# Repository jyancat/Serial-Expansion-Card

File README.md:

Design files for my DB9 RS232 Expansion Card 

JLCPCB production files are generated by [Bouni's JLCPCB tools plugin](https://github.com/bouni/kicad-jlcpcb-tools)

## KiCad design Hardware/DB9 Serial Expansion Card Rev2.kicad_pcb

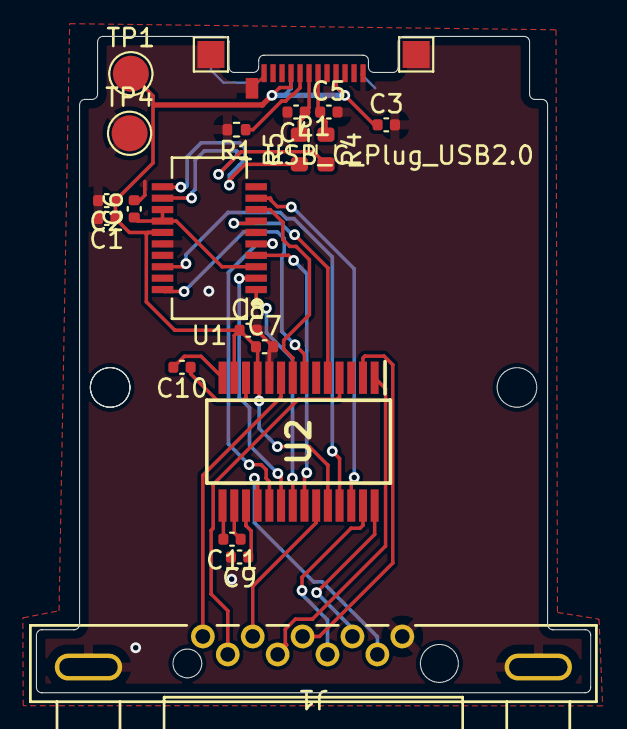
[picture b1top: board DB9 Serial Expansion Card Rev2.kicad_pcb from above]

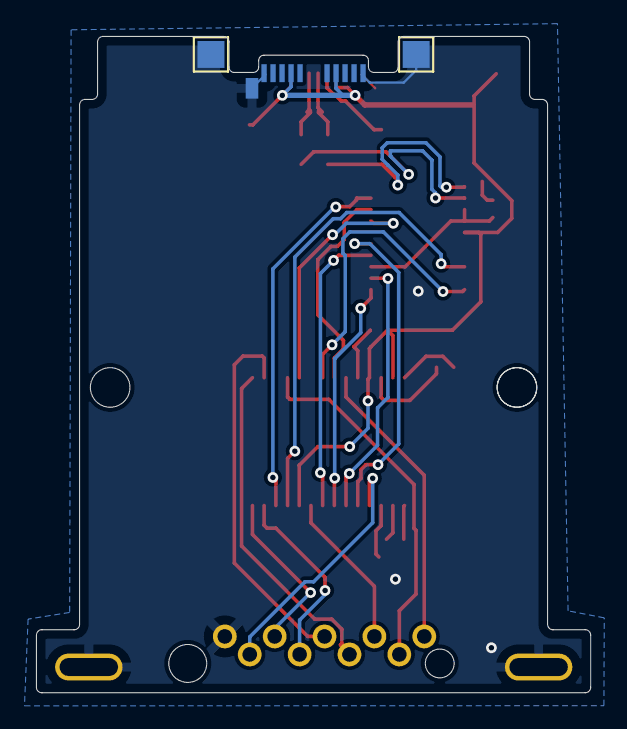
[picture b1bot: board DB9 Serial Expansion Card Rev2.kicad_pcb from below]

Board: 2 copper layers, 30.8 x 36.5 mm, 27 parts (2 on the bottom side), 28 nets.

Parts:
C1, C6, C7, C8, C10: 100nF; C_0402_1005Metric
C2: 4.7uF; C_0402_1005Metric
C3: 10nF; C_0402_1005Metric
C4, C5: 47pF; C_0402_1005Metric
C9, C11: 100nF, 16v; C_0402_1005Metric
H1, H1#2, H2: MountingHole; MountingHole_2.2mm_M2
J1: DE9_Receptacle; CONN9_K31X_KYC
P1: USB_C_Plug_USB2.0; USB_C_Plug_Molex_105444
R1: 5.1k; R_0402_1005Metric
R4, R5: 27R; R_0603_1608Metric
TP1, TP2, TP3, TP4#2: TestPoint; TestPoint_Pad_1.5x1.5mm
TP1#2, TP4: TestPoint; TestPoint_Pad_D2.0mm
U1: FT231XS; SSOP-20_3.9x8.7mm_P0.635mm
U2: SP213ECA-L_TR; SOP65P780X200-28N

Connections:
3V3OUT: C6.1, U1.3 (VCCIO), U1.13 (3V3OUT), U1.14 (~RESET)
/D+: C4.1, P1.A6 (D+), R5.1, R5.2, U1.11 (USBDP)
/D-: C5.1, P1.A7 (D-), R4.1, R4.2, U1.12 (USBDM)
CTS: J1.8, U2.27 (R3IN)
DCD: J1.1, U2.9 (R1IN)
DSR: J1.6, U2.4 (R2IN)
DTR: J1.4, U2.28 (T4OUT)
Earth: C1.2, C2.2, C3.2, C4.2, C5.2, C6.2, C7.2, C8.2, C9.2, J1.5, J1.10 (5), J1.11 (5), P1.A1 (GND), P1.A12 (GND), P1.B1 (GND), P1.B12 (GND), P1.S1 (SHIELD), R1.2, TP1.1, TP2.1, TP3.1, TP4.1, TP4#2.1, U1.6 (GND), U1.16 (GND), U2.10 (GND)
unnamed: P1.A5 (CC), R1.1
unnamed: C10.1, U2.12 (C1+)
unnamed: C10.2, U2.14 (C1-)
unnamed: C11.2, U2.15 (C2+)
unnamed: C11.1, U2.16 (C2-)
unnamed: C9.1, U2.17 (V-)
RI: J1.9, U2.18 (R5IN)
RTS: J1.7, U2.1 (T3OUT)
RXD: J1.2, U2.23 (R4IN)
SLEEP#: U1.18 (CBUS0), U2.25 (~SHUTDOWN_(SD))
TXD: J1.3, U2.2 (T1OUT)
USB_RXD: U1.4 (RXD), U2.22 (R4OUT)
USB_TXD: U1.20 (TXD), U2.7 (T1IN)
USB_~CTS: U1.9 (~CTS), U2.26 (R3OUT)
USB_~DCD: U1.8 (~DCD), U2.8 (R1OUT)
USB_~DSR: U1.7 (~DSR), U2.5 (R2OUT)
USB_~DTR: U1.1 (~DTR), U2.21 (T4IN)
USB_~RI: U1.5 (~RI), U2.19 (R5OUT)
USB_~RTS: U1.2 (~RTS), U2.20 (T3IN)
VCC: C1.1, C2.1, C3.1, C7.1, C8.1, P1.A4 (VBUS), P1.A9 (VBUS), P1.B4 (VBUS), P1.B9 (VBUS), TP1#2.1, U1.15 (VCC), U2.11 (VCC), U2.13 (V+), U2.24 (EN)

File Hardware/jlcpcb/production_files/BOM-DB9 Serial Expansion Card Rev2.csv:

Comment,Designator,Footprint,LCSC
FT231XS,U1,SSOP-20_3.9x8.7mm_P0.635mm,C132160
USB_C_Plug_USB2.0,P1,USB_C_Plug_Molex_105444,C134082
10nF,C3,C_0402_1005Metric,C15195
100nF,"C1,C10,C11,C6,C7,C8,C9",C_0402_1005Metric,C1525
SP213ECA-L_TR,U2,SOP65P780X200-28N,C1544521
47pF,"C4,C5",C_0402_1005Metric,C1567
DE9_Receptacle,J1,CONN9_K31X_KYC,C17429472
4.7uF,C2,C_0402_1005Metric,C23733
27R,"R4,R5",R_0603_1608Metric,C25190
5.1k,R1,R_0402_1005Metric,C25905

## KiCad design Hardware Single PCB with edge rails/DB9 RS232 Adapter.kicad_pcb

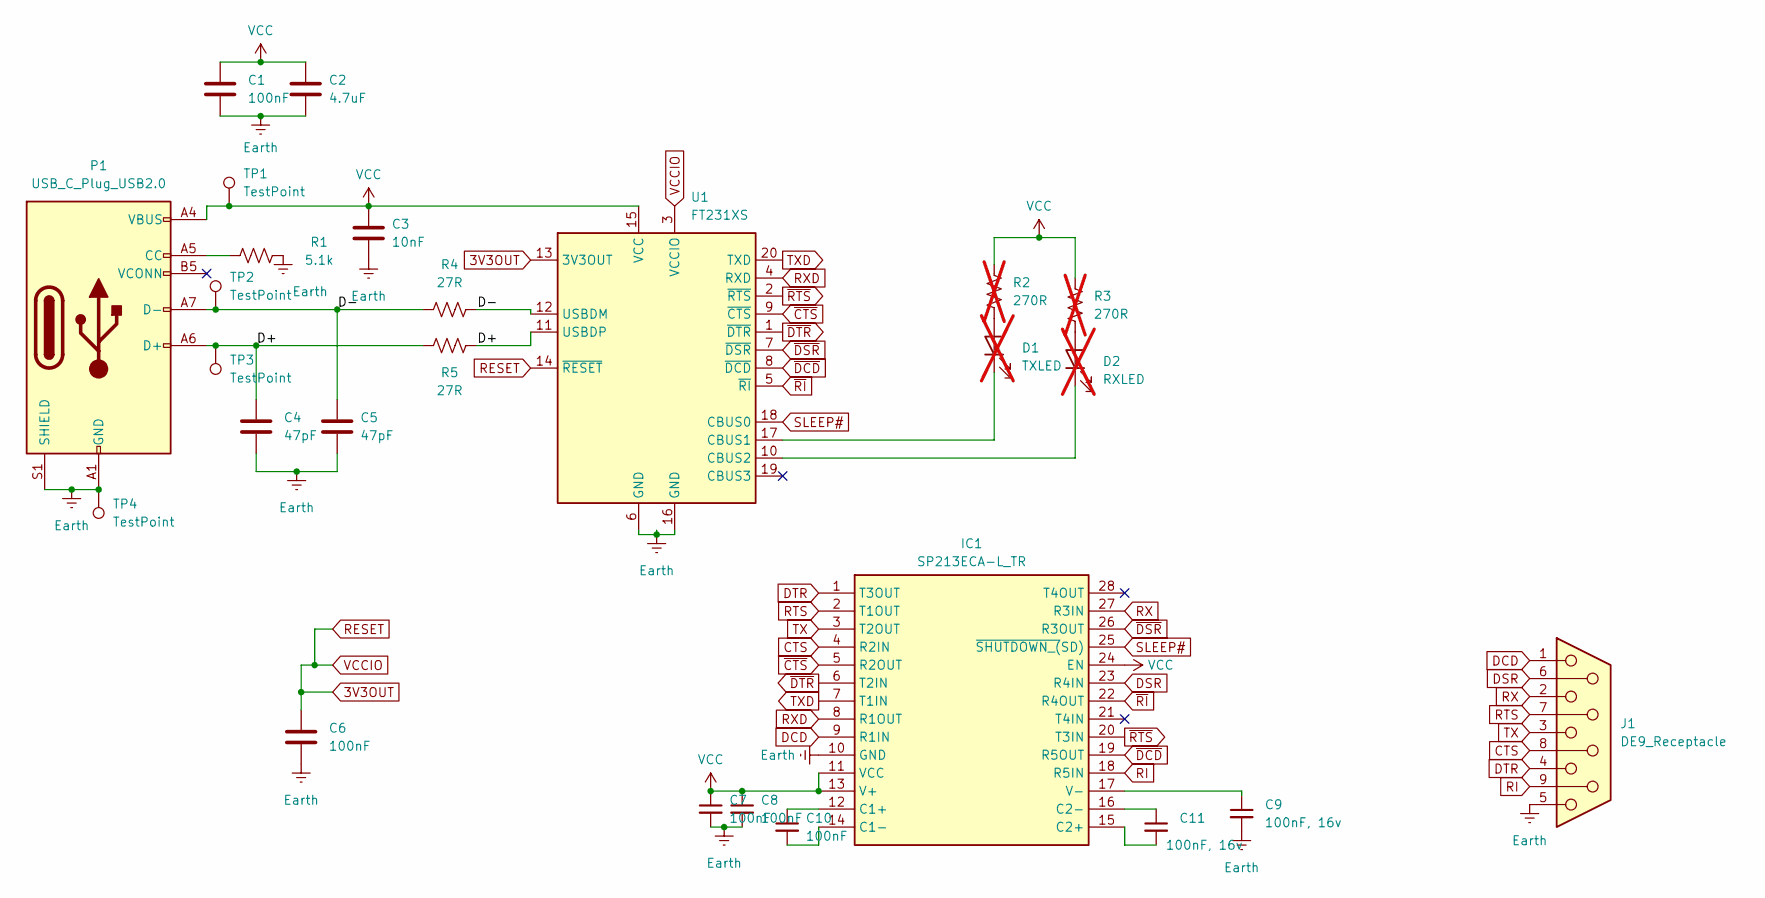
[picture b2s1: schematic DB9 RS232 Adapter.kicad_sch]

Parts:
C1, C6, C7, C8, C10: 100nF; C_0402_1005Metric
C2: 4.7uF; C_0402_1005Metric
C3: 10nF; C_0402_1005Metric
C4, C5: 47pF; C_0402_1005Metric
C9, C11: 100nF, 16v; C_0402_1005Metric
D1: TXLED; LED_0603_1608Metric; not fitted
D2: RXLED; LED_0603_1608Metric; not fitted
IC1: SP213ECA-L_TR; SOP65P780X200-28N; Manufacturer_Part_Number SP213ECA-L/TR; Mouser Part Number 701-SP213ECA-L/TR
J1: DE9_Receptacle; CONN9_K31X_KYC
P1: USB_C_Plug_USB2.0; USB_C_Plug_Molex_105444
R1: 5.1k; R_0402_1005Metric
R2, R3: 270R; R_0603_1608Metric; not fitted
R4, R5: 27R; R_0603_1608Metric
TP1, TP4: TestPoint; TestPoint_Pad_D2.0mm
TP2, TP3: TestPoint; TestPoint_Pad_1.0x1.0mm
U1: FT231XS; SSOP-20_3.9x8.7mm_P0.635mm

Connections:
3V3OUT: C6.1, U1.3 (VCCIO), U1.13 (3V3OUT), U1.14 (~RESET)
/D+: C4.1, P1.A6 (D+), R5.1, R5.2, TP3.1, U1.11 (USBDP)
/D-: C5.1, P1.A7 (D-), R4.1, R4.2, TP2.1, U1.12 (USBDM)
CTS: IC1.4 (R2IN), J1.8
DCD: IC1.9 (R1IN), J1.1
DSR: IC1.23 (R4IN), J1.6
DTR: IC1.1 (T3OUT), J1.4
unnamed: D1.2 (A), R2.2
unnamed: D1.1 (K), U1.17 (CBUS1)
unnamed: D2.2 (A), R3.2
unnamed: D2.1 (K), U1.10 (CBUS2)
unnamed: C10.1, IC1.12 (C1+)
unnamed: C10.2, IC1.14 (C1-)
unnamed: C11.2, IC1.15 (C2+)
unnamed: C11.1, IC1.16 (C2-)
unnamed: C9.1, IC1.17 (V-)
unnamed: P1.A5 (CC), R1.1
RI: IC1.18 (R5IN), J1.9
RTS: IC1.2 (T1OUT), J1.7
RX: IC1.27 (R3IN), J1.2
RXD: IC1.8 (R1OUT), U1.4 (RXD)
SLEEP#: IC1.25 (~SHUTDOWN_(SD)), U1.18 (CBUS0)
TX: IC1.3 (T2OUT), J1.3
TXD: IC1.7 (T1IN), U1.20 (TXD)
~CTS: IC1.5 (R2OUT), U1.9 (~CTS)
~DCD: IC1.19 (R5OUT), U1.8 (~DCD)
~DSR: IC1.26 (R3OUT), U1.7 (~DSR)
~DTR: IC1.6 (T2IN), U1.1 (~DTR)
~RI: IC1.22 (R4OUT), U1.5 (~RI)
~RTS: IC1.20 (T3IN), U1.2 (~RTS)

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
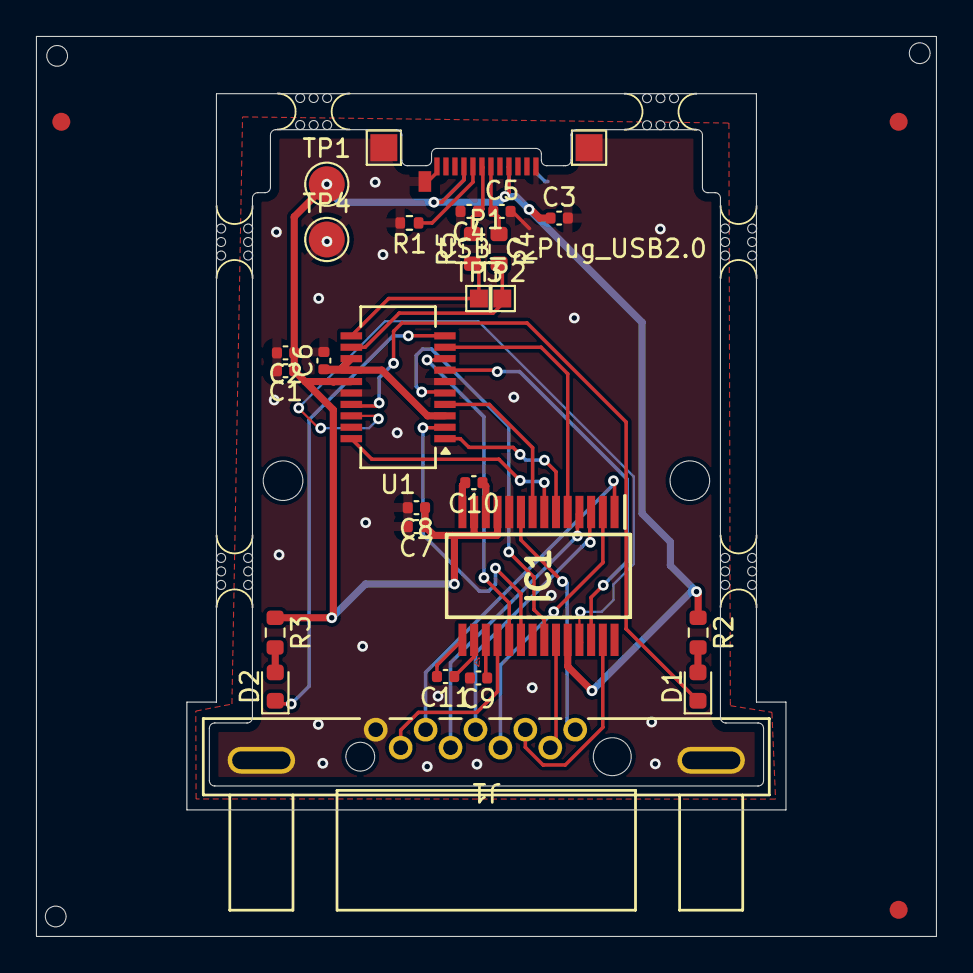
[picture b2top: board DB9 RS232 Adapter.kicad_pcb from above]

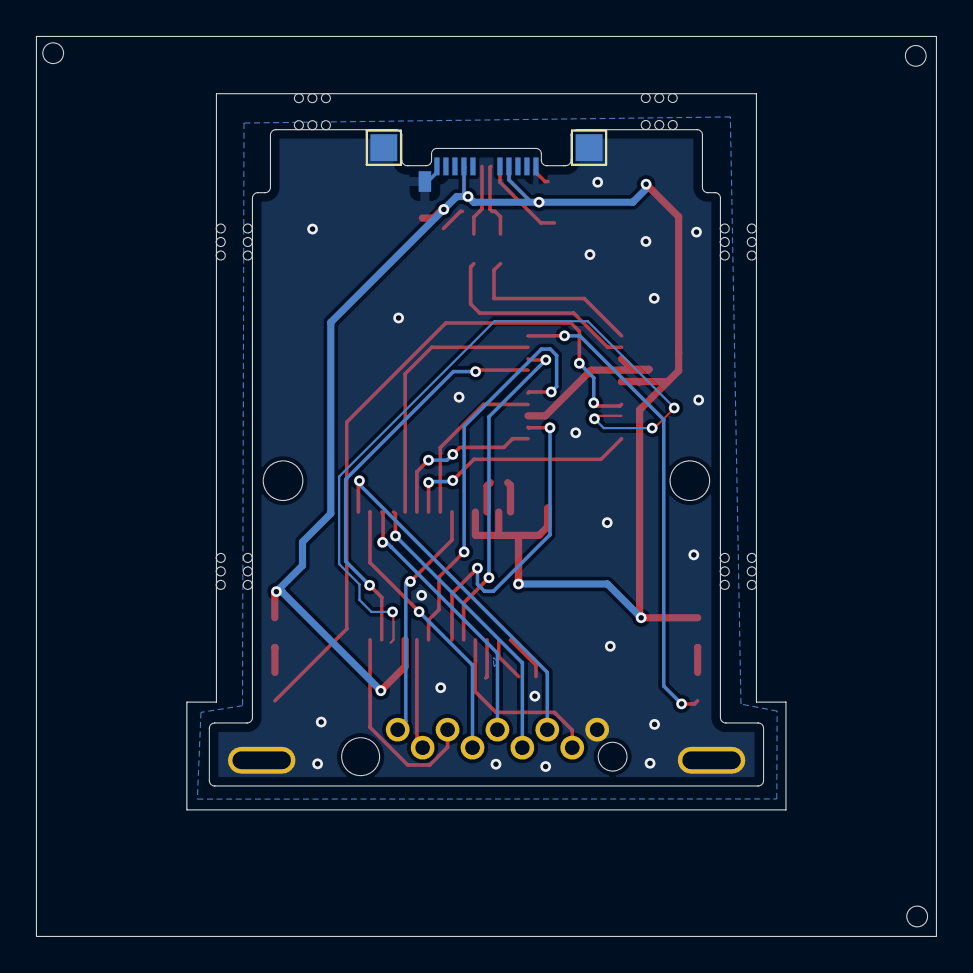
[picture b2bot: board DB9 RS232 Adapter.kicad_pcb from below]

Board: 2 copper layers, 50.0 x 50.0 mm, 38 parts (2 on the bottom side), 32 nets.

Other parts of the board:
H1, H2: MountingHole; MountingHole_2.2mm_M2
TP1#2: TestPoint; TestPoint_Pad_D2.0mm
TP2#2, TP3#2, TP4#2: TestPoint; TestPoint_Pad_1.5x1.5mm
mouse-bite-2mm-slot, mouse-bite-2mm-slot#2, mouse-bite-2mm-slot#3, mouse-bite-2mm-slot#4, mouse-bite-2mm-slot#5, mouse-bite-2mm-slot#6: VAL**; mouse-bite-2mm-slot

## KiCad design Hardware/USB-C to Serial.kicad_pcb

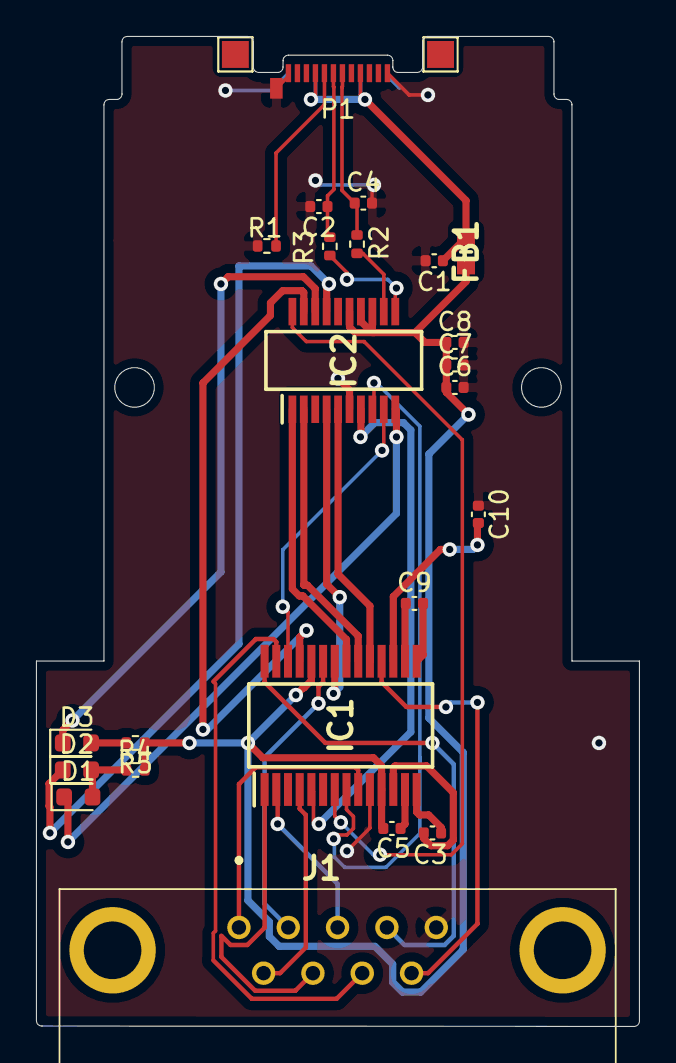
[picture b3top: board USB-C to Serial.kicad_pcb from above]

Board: 2 copper layers, 33.5 x 55.0 mm, 27 parts (0 on the bottom side), 36 nets.

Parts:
C1, C3, C5, C7, C8, C9, C10: 0.1uF; C_0402_1005Metric
C2, C4: 47pF; C_0402_1005Metric
C6: 4.7uF; C_0402_1005Metric
D1: RED RX; LED_0603_1608Metric
D2: BLUE TX; LED_0603_1608Metric
D3: GREEN PWR; LED_0603_1608Metric
FB1: 2A 220 OHM; BEADC1608X75N
H1, H2: MountingHole; MountingHole_2.2mm_M2
IC1: ZT213LEEA; SOP65P780X200-28N
IC2: FT231XS-R; SOP64P599X175-20N
J1: 5747844-4; 33381682
P1: USB_C_Plug_USB2.0; USB_C_Plug_Molex_105444
R1: 5.1K; R_0402_1005Metric
R2, R3: 27k; R_0402_1005Metric
R4, R5: 470R; R_0402_1005Metric
TP1, TP3: TestPoint; TestPoint_Pad_1.5x1.5mm

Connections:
CTS: IC1.27, J1.8
D+: IC2.11, R3.2
D-: IC2.12, R2.1
DCD: IC1.9, J1.1
DD+: C2.1, P1.A6, R3.1
DD-: C4.1, P1.A7, R2.2
DSR: IC1.4, J1.6
DTR: IC1.28, J1.4
EN: C5.1, C6.1, C7.1, C8.1, FB1.2, IC1.11, IC1.24, IC2.13, IC2.14, IC2.15, R4.1, R5.1
unnamed: C1.1, FB1.1, P1.A4, P1.A9, P1.B4, P1.B9
unnamed: C3.1, IC1.12
unnamed: C3.2, IC1.14
unnamed: C9.1, IC1.16
unnamed: C9.2, IC1.15
unnamed: C10.2, IC1.17
unnamed: D1.1, IC2.10
unnamed: D1.2, D2.2, R4.2
unnamed: D2.1, IC2.17
unnamed: D3.1, IC2.18
unnamed: D3.2, R5.2
unnamed: P1.A5, R1.1
RI: IC1.18, J1.9
RTS: IC1.1, J1.7
RXD: IC1.23, J1.2
SLEEP: IC1.25, IC2.19
TXD: IC1.2, J1.3
USBCTS: IC1.26, IC2.9
USBDCD: IC1.8, IC2.8
USBDSR: IC1.5, IC2.7
USBDTR: IC1.21, IC2.1
USBRI: IC1.19, IC2.5
USBRTS: IC1.20, IC2.2
USBRXD: IC1.22, IC2.4
USBTXD: IC1.7, IC2.20
V+: C5.2, IC1.13
V-: C1.2, C2.2, C4.2, C6.2, C7.2, C8.2, C10.1, IC1.10, IC2.6, J1.5, P1.A1, P1.A12, P1.B1, P1.B12, P1.S1, R1.2

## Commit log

2022-05-04 Updated Files
2022-05-04 Updated PDF
2024-03-30 Merged local and GitHub folders
    added all design files, updated gitignore
2024-03-30 Update LICENCE.md to latest version
2024-03-31 Added enclosure files
2024-04-08 Added final production file
2024-08-14 Updated to final production revision
2024-08-14 Updated licence
